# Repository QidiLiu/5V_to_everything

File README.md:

# 5V_to_everything

Convert *5V (from microUSB)* to various *positive and negative voltages* (for **small currents** only) at low cost with the TPS61040.

## Low cost version

### Setting and Usage

Most smartphone chargers can convert 220VAC to 5VDC. With this "5V_to_every" converter, electronic engineers can easily get a positive and negative voltage source, which has an **output voltage from ±5V to ±24V** using their smartphone chargers.

The basic idea comes from [datasheet of TPS61040](https://www.ti.com/lit/ds/symlink/tps61040.pdf). The output voltage can configured by changing the ratio of R1 to R2. In my design, R2 is 1kΩ SMD resistor and R1 can be easily replaced with a suitable resistor accourding to the calculation:

V_out = 1.233V × (1 + R1/R2) 

(V+ = V_out; V- = -V_out)

(range of V_out: 5V~24V)

For example, if you want a ±10V voltage source:

10 = 1.233 × (1 + R1/1000)

→ R1 = 7110 [Ω]

That means you should replace R1 with a 7.1kΩ resistor.

I also recommend you to replace R1 with a **potentiometer (20kΩ)**, so you can adjust the output voltage directly by hand, and reuse this voltage source in different projects, even when they demand different voltages.

## Minimum size version with microUSB

min_size_microUSB is a minimum size version of 5V_to_everything.

Size of min_size_microUSB[mm]: **14 x 10 x 6**

## Planned versions

- Minimum size version with typeC

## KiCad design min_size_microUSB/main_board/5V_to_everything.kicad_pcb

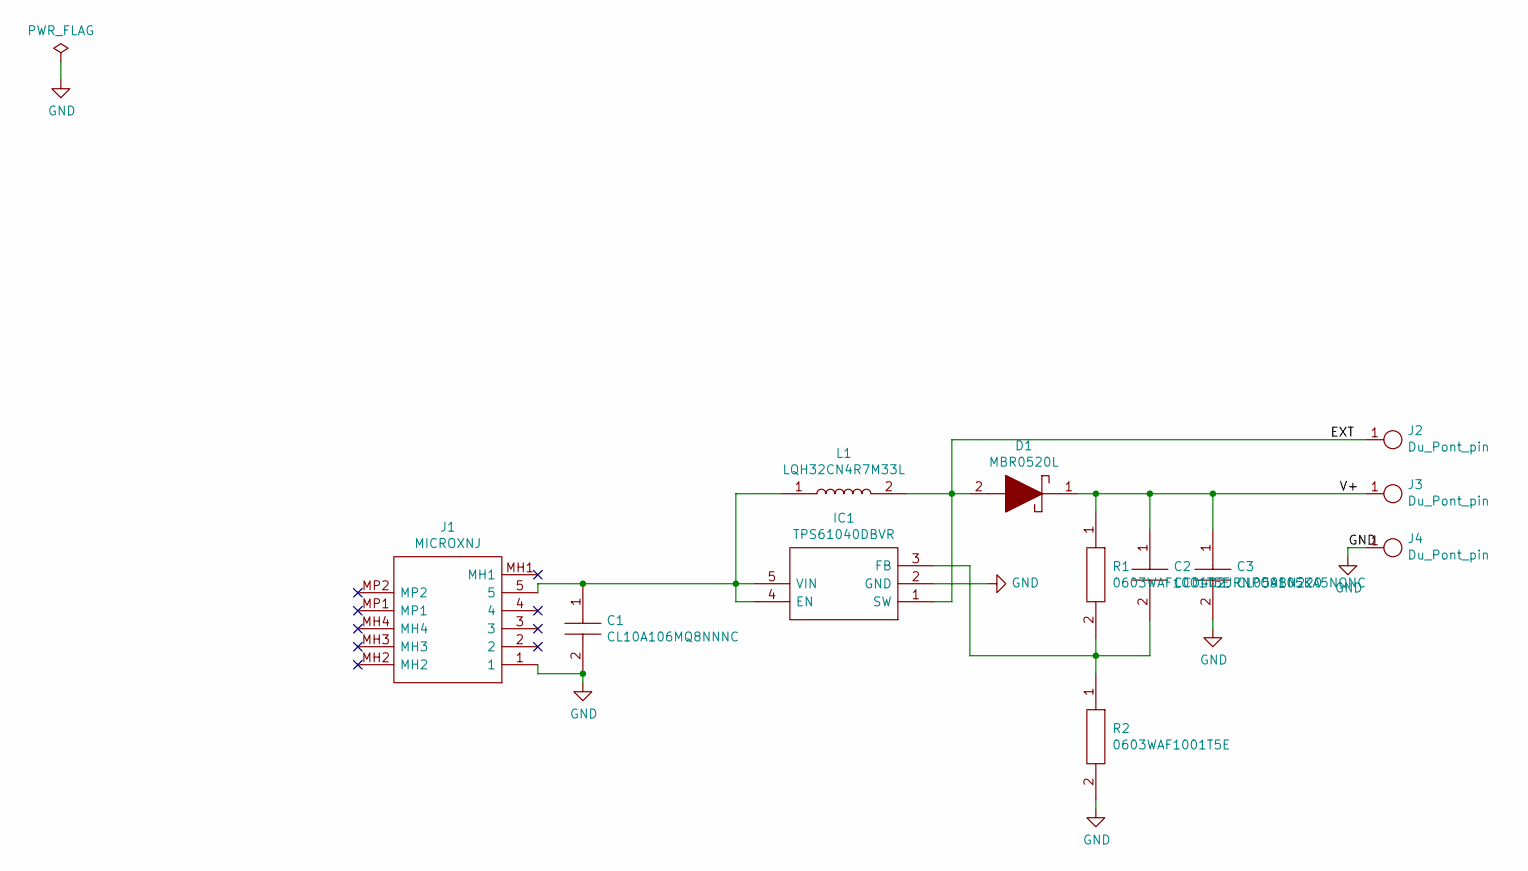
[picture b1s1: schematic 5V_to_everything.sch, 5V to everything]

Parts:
C1: CL10A106MQ8NNNC; CAPC1608X90N; Manufacturer_Part_Number CL10A106MQ8NNNC; Mouser Part Number 187-CL10A106MQ8NNNC
C2: CC0402JRNPO9BN220; CAPC1005X55N; Manufacturer_Part_Number CC0402JRNPO9BN220; Mouser Part Number 603-CC402JRNPO9BN220
C3: CL05A105KA5NQNC; CAPC1005X60N; Manufacturer_Part_Number CL05A105KA5NQNC; Mouser Part Number 187-CL05A105KA5NQNC
D1: MBR0520L; SOD3816X128N; Manufacturer_Part_Number MBR0520L; Mouser Part Number 512-MBR0520L
IC1: TPS61040DBVR; SOT95P280X145-5N; Manufacturer_Part_Number TPS61040DBVR; Mouser Part Number 595-TPS61040DBVR
J1: MICROXNJ; Manufacturer_Part_Number MICROXNJ
J2, J3, J4: Du_Pont_pin
L1: LQH32CN4R7M33L; LQH32DN100K23L; Manufacturer_Part_Number LQH32CN4R7M33L; Mouser Part Number 81-LQH32CN4R7M33L
R1, R2: 0603WAF1001T5E; RESC1608X55N; Manufacturer_Part_Number 0603WAF1001T5E

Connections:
/EXT: D1.2, IC1.1 (SW), J2.1, L1.2
/V+: C2.1, C3.1, D1.1, J3.1, R1.1
GND: C1.2, C3.2, IC1.2 (GND), J1.1, J4.1, R2.2
unnamed: C1.1, IC1.4 (EN), IC1.5 (VIN), J1.5, L1.1
unnamed: C2.2, IC1.3 (FB), R1.2, R2.1

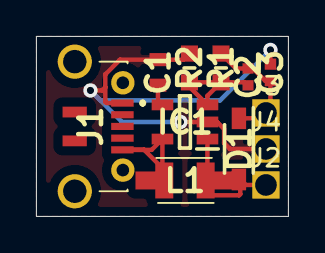
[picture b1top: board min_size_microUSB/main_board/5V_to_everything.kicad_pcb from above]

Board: 2 copper layers, 14.0 x 10.0 mm, 12 parts (0 on the bottom side), 5 nets.

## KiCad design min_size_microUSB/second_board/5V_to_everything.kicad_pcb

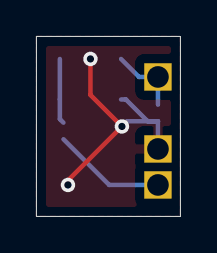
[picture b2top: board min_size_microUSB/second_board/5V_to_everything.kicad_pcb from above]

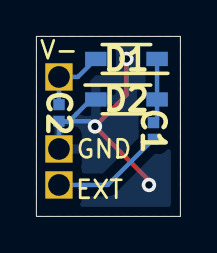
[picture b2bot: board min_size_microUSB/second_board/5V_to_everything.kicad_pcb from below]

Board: 2 copper layers, 8.0 x 10.0 mm, 7 parts (7 on the bottom side), 4 nets.

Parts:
C1, C2: CL05A105KA5NQNC; CAPC1005X60N
D1, D2: MBR0520L; SOD3816X128N
EXT: Du_Pont_pin
GND: Du_Pont_pin
V-: Du_Pont_pin

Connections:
GND: C2.2, D2.1, GND.1
unnamed: C1.1, D1.1, D2.2
unnamed: C1.2, EXT.1
unnamed: C2.1, D1.2, V-.1

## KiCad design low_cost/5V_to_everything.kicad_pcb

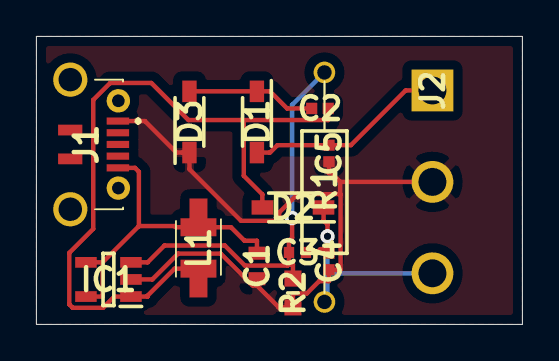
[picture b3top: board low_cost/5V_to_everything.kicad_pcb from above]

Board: 2 copper layers, 27.0 x 16.0 mm, 14 parts (0 on the bottom side), 7 nets.

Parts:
C1: CL10A106MQ8NNNC; CAPC1608X90N
C2, C4, C5: CL05A105KA5NQNC; CAPC1005X60N
C3: CC0402JRNPO9BN220; CAPC1005X55N
D1, D2, D3: MBR0520L; SOD3816X128N
IC1: TPS61040DBVR; SOT95P280X145-5N
J1: MICROXNJ
J2: WJ500V-5.08-3P; SHDR3W95P0X508_1X3_1524X1000X1420P
L1: LQH32CN4R7M33L; LQH32DN100K23L
R1: MFR0W4F1001A50; RESAD1680W62L680D250
R2: 0603WAF1001T5E; RESC1608X55N

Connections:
/V+: C3.1, C4.1, D2.1, J2.3, R1.1
/V-: C5.1, D1.2, J2.1
GND: C1.2, C4.2, C5.2, D3.1, IC1.2, J1.1, J2.2, R2.2
unnamed: C1.1, IC1.4, IC1.5, J1.5, L1.1
unnamed: C2.1, D1.1, D3.2
unnamed: C2.2, D2.2, IC1.1, L1.2
unnamed: C3.2, IC1.3, R1.2, R2.1

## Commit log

2021-07-24 Files moved to folders
2021-07-24 min_size_microUSB
